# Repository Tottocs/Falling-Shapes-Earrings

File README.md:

# Falling Shapes Earrings
Earrings that display a falling shapes animation with an LED matrix. Made for my dear girlfriend. PCB designed in KiCad.

## License

This project is licensed under the Creative Commons Attribution-NonCommercial 4.0 International License (CC BY-NC 4.0).

Commercial use is not permitted.

See the LICENSE file for details.

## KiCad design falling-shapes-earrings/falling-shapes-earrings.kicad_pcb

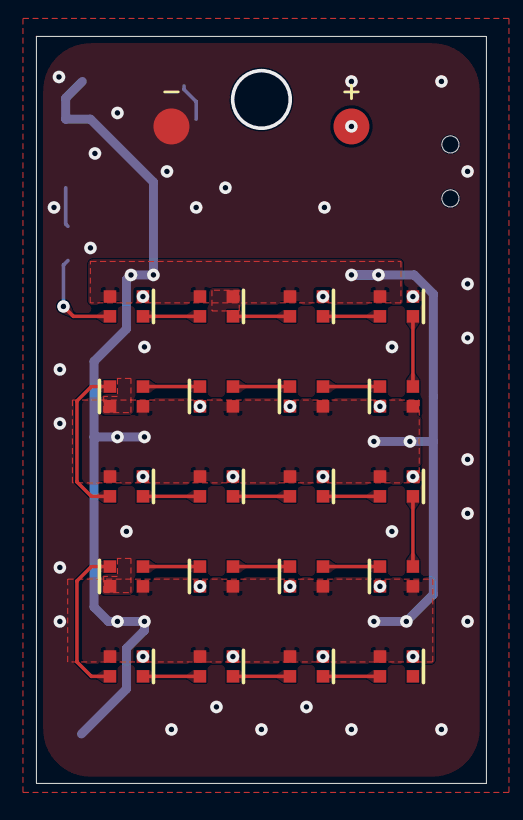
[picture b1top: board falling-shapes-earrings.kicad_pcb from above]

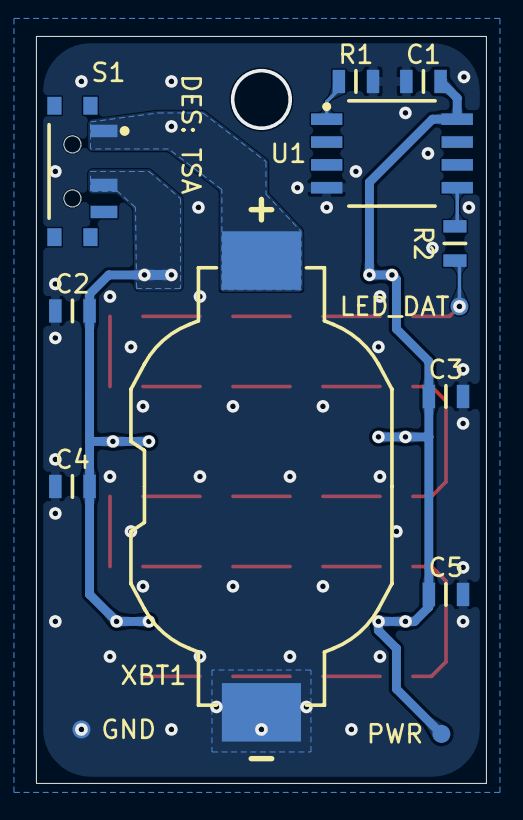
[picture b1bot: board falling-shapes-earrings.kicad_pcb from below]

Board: 2 copper layers, 25.0 x 41.5 mm, 35 parts (13 on the bottom side), 25 nets.

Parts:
C1, C2, C3, C4, C5: 100nF; C0805_0.25
D1, D2, D3, D4, D5, D6, D7, D8, D9, D10, D11, D12, D13, D14, D15, D16, D17, D18, D19, D20: WS2812B-2020-V6
R1: 10k; R0805_0_25
R2: 100R; R0805_0_25
S1: CUS-12TB; CUS12TB
TP1: LED_DAT; 1mm Test Pad
TP2: PWR; 1mm Test Pad
TP3: GND; 1mm Test Pad
TP4: +; 2mm Test Pad
TP5: -; 2mm Test Pad
U1: ATTINY85-20SUR; SOIC-8N (MS-012)
XBT1: SMTU1632-LF; SMTU1632LF

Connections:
3.3V: C1.2, C2.2, C3.2, C4.2, C5.2, D1.4 (VDD), D2.4 (VDD), D3.4 (VDD), D4.4 (VDD), D5.4 (VDD), D6.4 (VDD), D7.4 (VDD), D8.4 (VDD), D9.4 (VDD), D10.4 (VDD), D11.4 (VDD), D12.4 (VDD), D13.4 (VDD), D14.4 (VDD), D15.4 (VDD), D16.4 (VDD), D17.4 (VDD), D18.4 (VDD), D19.4 (VDD), D20.4 (VDD), S1.2, TP2.1 (Test_1), U1.8 (VCC)
/COIN_PWR: S1.1, TP4.1 (Test_1), XBT1.1
/LED_DAT: D1.3 (DI), R2.2, TP1.1 (Test_1)
GNDREF: C1.1, C2.1, C3.1, C4.1, C5.1, D1.2 (GND), D2.2 (GND), D3.2 (GND), D4.2 (GND), D5.2 (GND), D6.2 (GND), D7.2 (GND), D8.2 (GND), D9.2 (GND), D10.2 (GND), D11.2 (GND), D12.2 (GND), D13.2 (GND), D14.2 (GND), D15.2 (GND), D16.2 (GND), D17.2 (GND), D18.2 (GND), D19.2 (GND), D20.2 (GND), R1.1, TP3.1 (Test_1), TP5.1 (Test_1), U1.4 (GND), XBT1.2
unnamed: D1.1 (DO), D6.3 (DI)
unnamed: D2.1 (DO), D7.3 (DI)
unnamed: D3.1 (DO), D8.3 (DI)
unnamed: D4.1 (DO), D9.3 (DI)
unnamed: D5.1 (DO), D10.3 (DI)
unnamed: D10.1 (DO), D15.3 (DI)
unnamed: D6.1 (DO), D11.3 (DI)
unnamed: D11.1 (DO), D16.3 (DI)
unnamed: D7.1 (DO), D12.3 (DI)
unnamed: D12.1 (DO), D17.3 (DI)
unnamed: D8.1 (DO), D13.3 (DI)
unnamed: D13.1 (DO), D18.3 (DI)
unnamed: D9.1 (DO), D14.3 (DI)
unnamed: D14.1 (DO), D19.3 (DI)
unnamed: D15.1 (DO), D20.3 (DI)
unnamed: D2.3 (DI), D16.1 (DO)
unnamed: D3.3 (DI), D17.1 (DO)
unnamed: D4.3 (DI), D18.1 (DO)
unnamed: D5.3 (DI), D19.1 (DO)
unnamed: R2.1, U1.5 (PB0)
unnamed: R1.2, U1.1 (PB5)

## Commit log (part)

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2026-04-07 Update LICENSE
    Creative Commons Attribution-NonCommercial 4.0 International
2026-04-07 Update LICENSE
    Added name
2026-04-07 Update README.md
    Added licence info
2026-04-07 Update README.md
    Changed name to falling shape
2026-04-07 Added KiCad Project
2026-04-07 Update .gitignore
    Ignore .history
